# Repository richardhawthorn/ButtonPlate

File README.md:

### Features

- ESP8266
- ATMega328p
- Capacitive Button pads
- 12 Charlieplex LEDs
- 3.3V operation
- Mini USB power connector
- FTDI programming port

### License

This work is licensed under a Creative Commons Attribution-ShareAlike 4.0 International License.

<br />
Designed by <a xmlns:cc="http://creativecommons.org/ns#" href="http://www.richardhawthorn.com" property="cc:attributionName" rel="cc:attributionURL" target="_blank">Richard Hawthorn</a><br />
<a rel="license" href="http://creativecommons.org/licenses/by-sa/4.0/" target="_blank">View License</a>

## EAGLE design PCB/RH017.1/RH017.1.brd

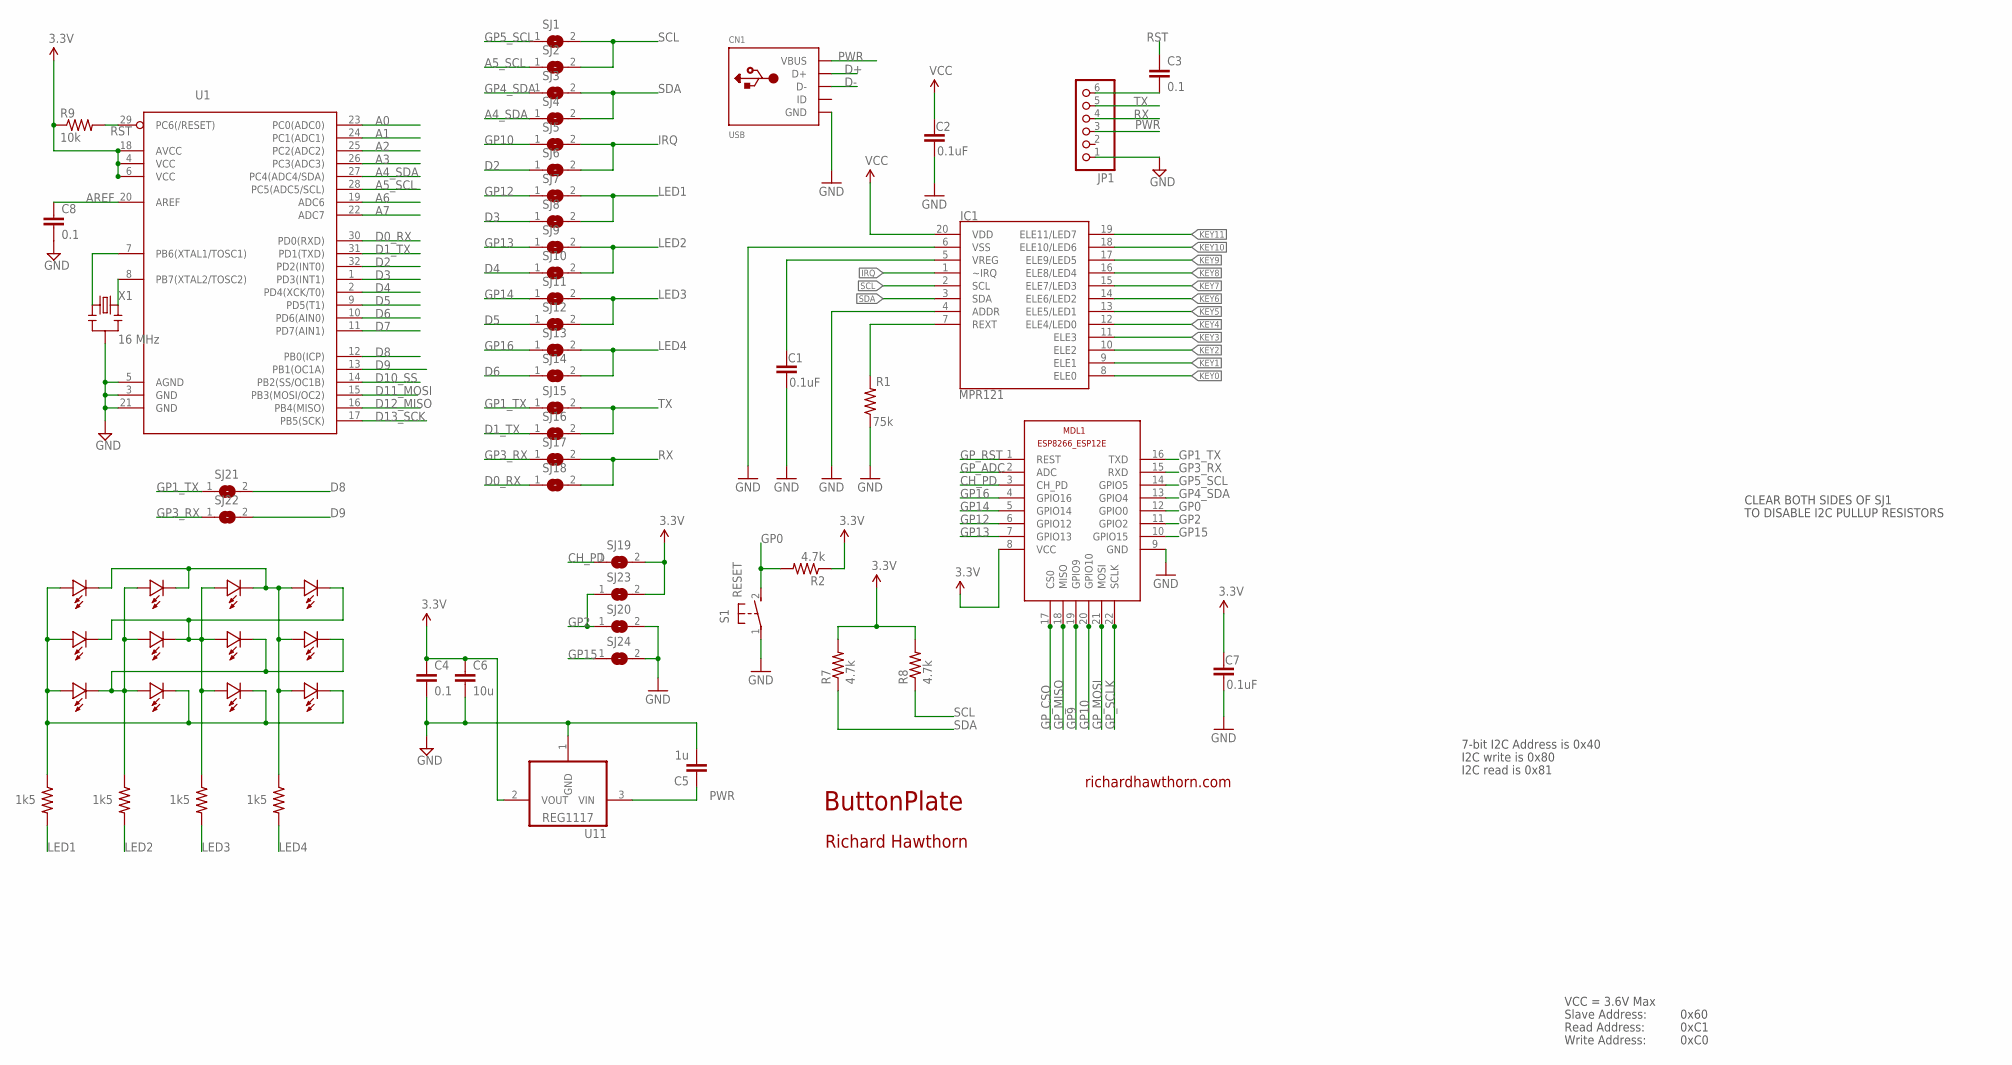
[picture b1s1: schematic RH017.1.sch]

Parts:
C1, C2, C7: 0.1uF; 0603-CAP
C3, C4, C8: 0.1; 0603-CAP
C5: 1u; 0603-CAP
C6: 10u; 0805-CAP
CN1: USB; USB-MINIB
IC1: MPR121; QFN-20-0.4MM-V2
JP1: PINHD-1X6; 1X06
LED1, LED2, LED3, LED4, LED5, LED6, LED7, LED8, LED9, LED10, LED11, LED12: LED0603; 0603-LED
MDL1: ESP8266-12EESP8266-ESP12E; ESP8266-ESP12E
R1: 75k; 0603-RES
R2, R7, R8: 4.7k; 0805
R3, R4, R5, R6: 1k5; 0603-RES
R9: 10k; 0603-RES
S1: RESET; DTSM-3
SJ1, SJ2, SJ3, SJ4, SJ5, SJ6, SJ7, SJ8, SJ9, SJ10, SJ11, SJ12, SJ13, SJ14, SJ15, SJ16, SJ17, SJ18, SJ19, SJ20, SJ21, SJ22, SJ23, SJ24: SJ
U1: ATMega-328; TQFP32-08
U11: REG1117; SOT223
X1: 16 MHz; RESONATOR-SMD

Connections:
3.3V: C2.1, C4.1, C6.1, C7.1, IC1.20 (VDD), MDL1.8 (VCC), R2.1, R7.2, R8.2, R9.1, SJ19.2, SJ23.2, U1.4 (VCC), U1.6 (VCC), U1.18 (AVCC), U11.2 (VOUT)
A0: U1.23 (PC0(ADC0))
A1: U1.24 (PC1(ADC1))
A2: U1.25 (PC2(ADC2))
A3: U1.26 (PC3(ADC3))
A4_SDA: SJ4.1, U1.27 (PC4(ADC4/SDA))
A5_SCL: SJ2.1, U1.28 (PC5(ADC5/SCL))
A6: U1.19 (ADC6)
A7: U1.22 (ADC7)
AREF: C8.1, U1.20 (AREF)
CH_PD: MDL1.3 (CH_PD), SJ19.1
D0_RX: SJ18.1, U1.30 (PD0(RXD))
D1_TX: SJ16.1, U1.31 (PD1(TXD))
D2: SJ6.1, U1.32 (PD2(INT0))
D3: SJ8.1, U1.1 (PD3(INT1))
D4: SJ10.1, U1.2 (PD4(XCK/T0))
D5: SJ12.1, U1.9 (PD5(T1))
D6: SJ14.1, U1.10 (PD6(AIN0))
D7: U1.11 (PD7(AIN1))
D8: SJ21.2, U1.12 (PB0(ICP))
D9: SJ22.2, U1.13 (PB1(OC1A))
D10_SS: U1.14 (PB2(SS/OC1B))
D11_MOSI: U1.15 (PB3(MOSI/OC2))
D12_MISO: U1.16 (PB4(MISO))
D13_SCK: U1.17 (PB5(SCK))
D+: CN1.D+
D-: CN1.D-
GND: C1.2, C2.2, C4.2, C5.2, C6.2, C7.2, C8.2, CN1.GND, IC1.4 (ADDR), IC1.6 (VSS), JP1.1, MDL1.9 (GND), R1.1, S1.1, SJ20.2, SJ24.2, U1.3 (GND), U1.5 (AGND), U1.21 (GND), U11.1 (GND), X1.2
GP0: MDL1.12 (GPIO0), R2.2, S1.2
GP1_TX: MDL1.16 (TXD), SJ15.1, SJ21.1
GP2: MDL1.11 (GPIO2), SJ20.1, SJ23.1
GP3_RX: MDL1.15 (RXD), SJ17.1, SJ22.1
GP4_SDA: MDL1.13 (GPIO4), SJ3.1
GP5_SCL: MDL1.14 (GPIO5), SJ1.1
GP9: MDL1.19 (GPIO9)
GP10: MDL1.20 (GPIO10), SJ5.1
GP12: MDL1.6 (GPIO12), SJ7.1
GP13: MDL1.7 (GPIO13), SJ9.1
GP14: MDL1.5 (GPIO14), SJ11.1
GP15: MDL1.10 (GPIO15), SJ24.1
GP16: MDL1.4 (GPIO16), SJ13.1
GP_ADC: MDL1.2 (ADC)
GP_CSO: MDL1.17 (CS0)
GP_MISO: MDL1.18 (MISO)
GP_MOSI: MDL1.21 (MOSI)
GP_RST: MDL1.1 (REST)
GP_SCLK: MDL1.22 (SCLK)
IRQ: IC1.1 (~IRQ), SJ5.2, SJ6.2
KEY0: IC1.8 (ELE0)
KEY1: IC1.9 (ELE1)
KEY2: IC1.10 (ELE2)
KEY3: IC1.11 (ELE3)
KEY4: IC1.12 (ELE4/LED0)
KEY5: IC1.13 (ELE5/LED1)
KEY6: IC1.14 (ELE6/LED2)
KEY7: IC1.15 (ELE7/LED3)
KEY8: IC1.16 (ELE8/LED4)
KEY9: IC1.17 (ELE9/LED5)
KEY10: IC1.18 (ELE10/LED6)
KEY11: IC1.19 (ELE11/LED7)
LED1: R3.2, SJ7.2, SJ8.2
LED2: R4.2, SJ9.2, SJ10.2
LED3: R5.2, SJ11.2, SJ12.2
LED4: R6.2, SJ13.2, SJ14.2
unnamed: U1.7 (PB6(XTAL1/TOSC1)), X1.1
unnamed: LED2.PLUS, LED6.PLUS, LED7.MINUS, LED8.MINUS, LED9.MINUS, LED10.PLUS, R4.1
unnamed: C3.2, JP1.6
unnamed: U1.8 (PB7(XTAL2/TOSC2)), X1.3
unnamed: LED1.PLUS, LED5.PLUS, LED9.PLUS, LED10.MINUS, LED11.MINUS, LED12.MINUS, R3.1
unnamed: LED1.MINUS, LED2.MINUS, LED3.MINUS, LED4.PLUS, LED8.PLUS, LED12.PLUS, R6.1
unnamed: LED3.PLUS, LED4.MINUS, LED5.MINUS, LED6.MINUS, LED7.PLUS, LED11.PLUS, R5.1
PWR: C5.1, CN1.VBUS, JP1.3, U11.3 (VIN)
REXT: IC1.7 (REXT), R1.2
RST: C3.1, R9.2, U1.29 (PC6(/RESET))
RX: JP1.4, SJ17.2, SJ18.2
SCL: IC1.2 (SCL), R8.1, SJ1.2, SJ2.2
SDA: IC1.3 (SDA), R7.1, SJ3.2, SJ4.2
TX: JP1.5, SJ15.2, SJ16.2
VREG: C1.1, IC1.5 (VREG)

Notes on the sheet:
ButtonPlate
richardhawthorn.com
Richard Hawthorn
CLEAR BOTH SIDES OF SJ1
TO DISABLE I2C PULLUP RESISTORS
7-bit I2C Address is 0x40
I2C write is 0x80
I2C read is 0x81
VCC = 3.6V Max
Read Address:
Write Address:
Slave Address:
0x60
0xC1
0xC0

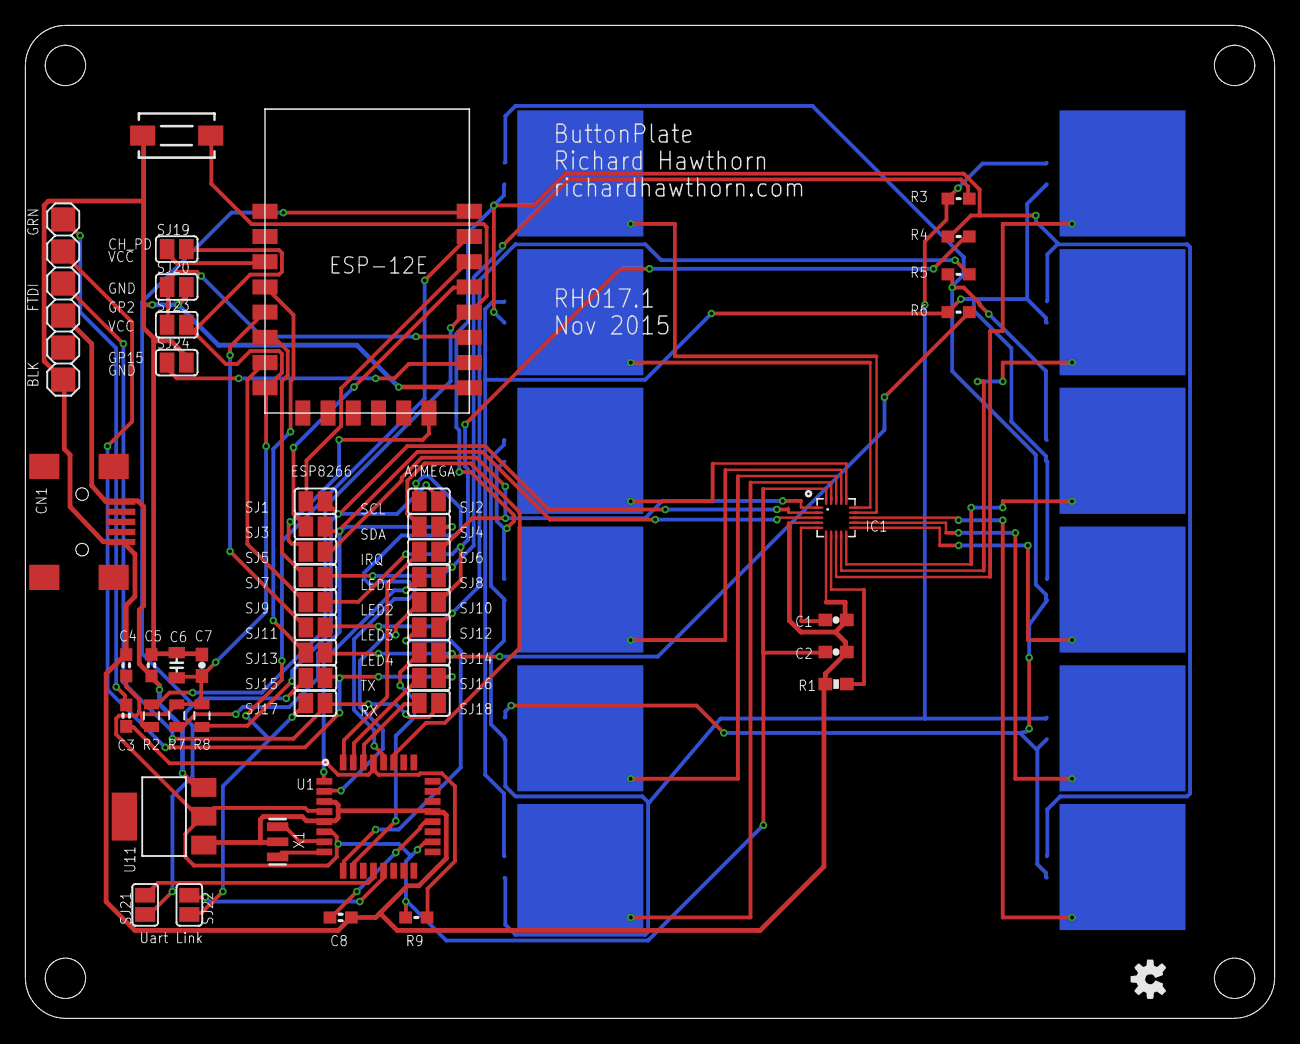
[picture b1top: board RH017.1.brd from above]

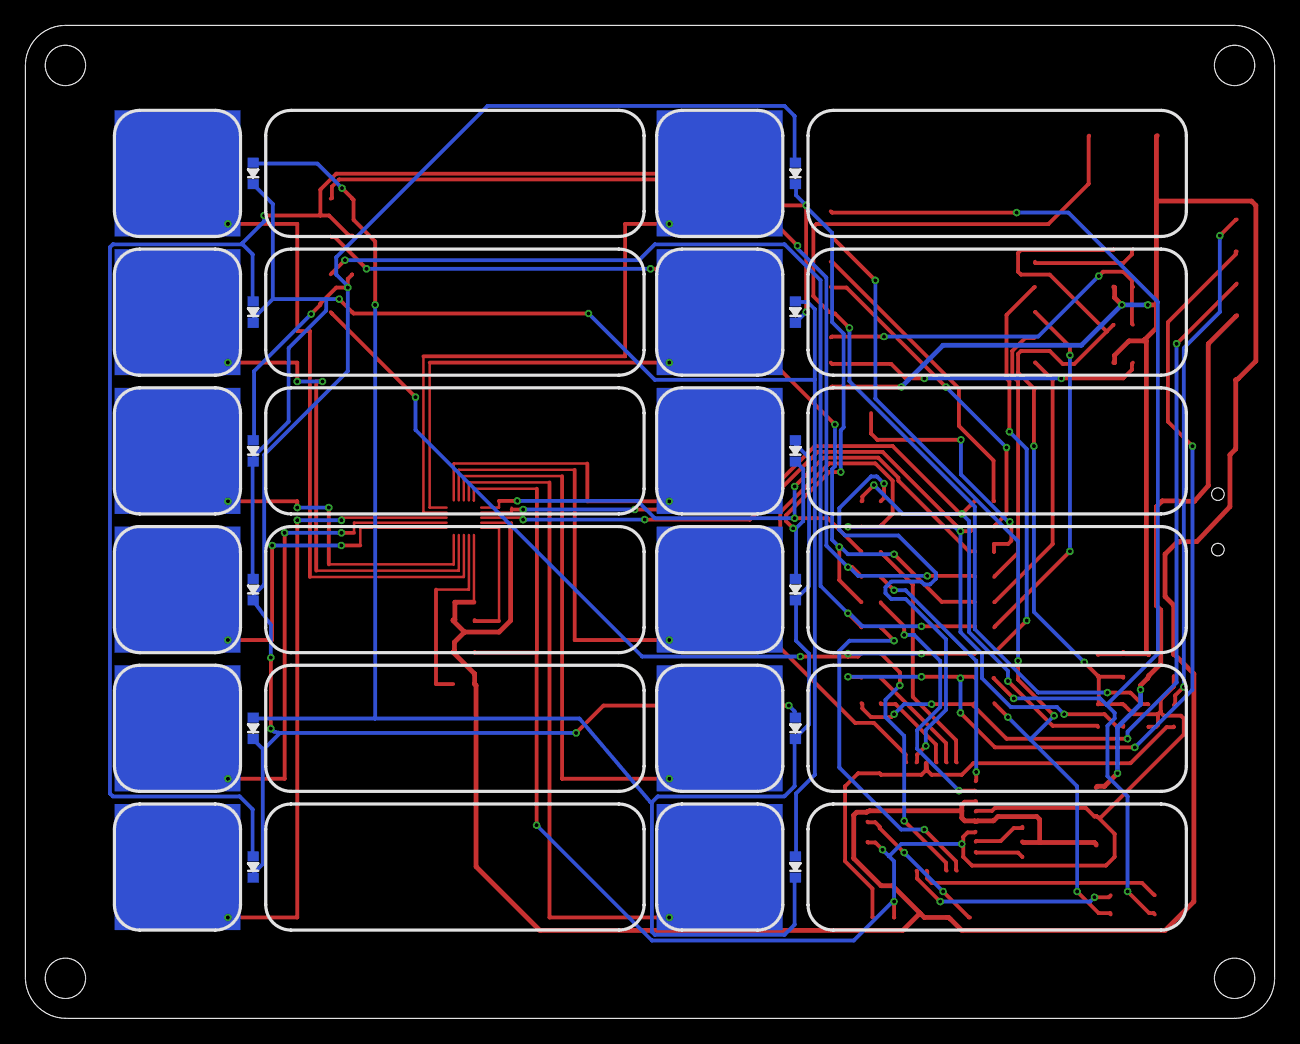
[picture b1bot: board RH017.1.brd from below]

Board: 2 copper layers, 99.1 x 78.7 mm, 62 parts (12 on the bottom side), 47 nets.

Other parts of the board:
U$3: OSHW-LOGO-S

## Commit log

2015-11-05 First version added
2015-11-05 added back image
2015-11-05 updated images
2015-11-05 added gerbers
2016-11-10 added readme

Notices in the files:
parts and their libraries:
SparkFun-Aesthetics: Licensing: CC v3.0 Share-Alike You are welcome to use this library for commercial purposes.
